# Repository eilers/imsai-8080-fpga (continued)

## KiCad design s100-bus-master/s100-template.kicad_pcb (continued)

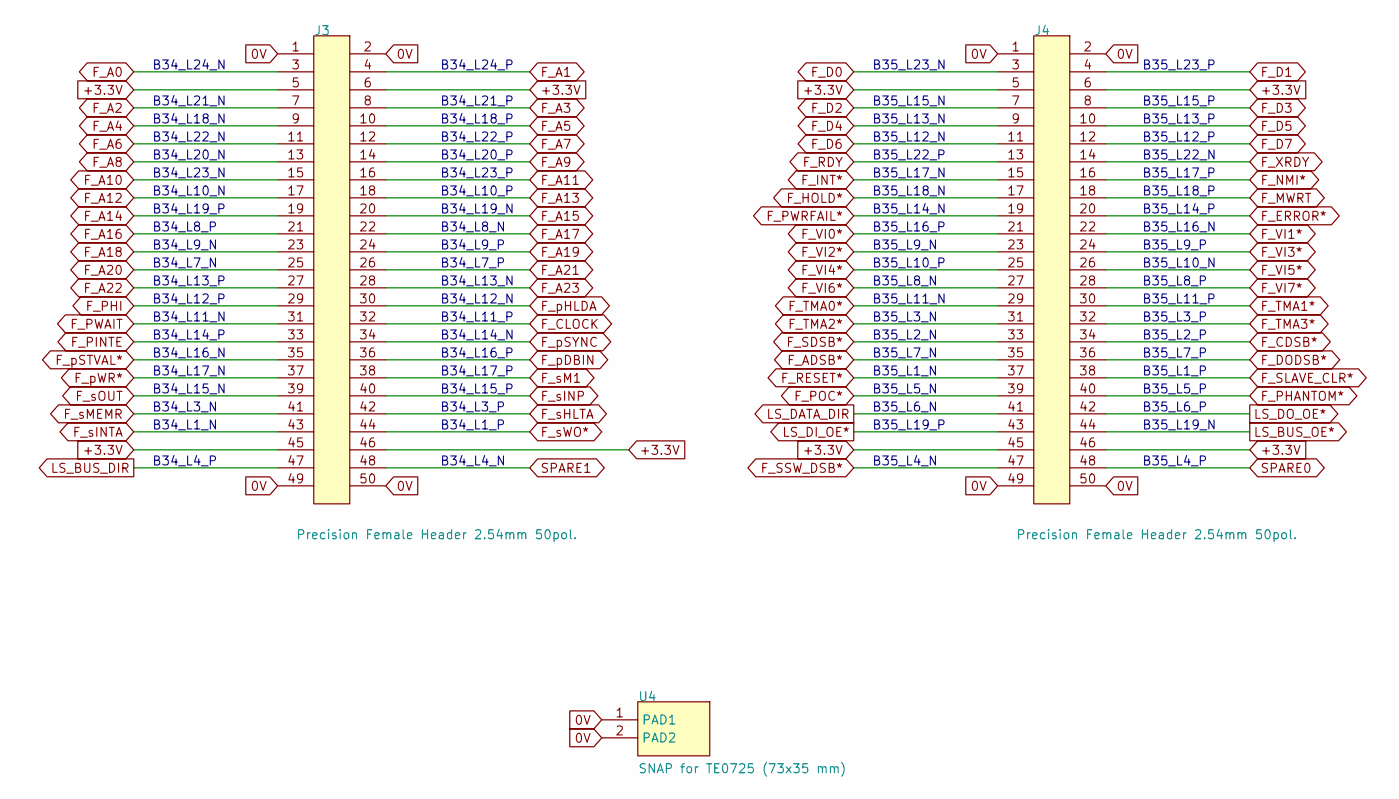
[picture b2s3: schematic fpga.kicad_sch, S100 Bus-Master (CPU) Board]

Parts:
J3, J4: Precision Female Header 2.54mm 50pol.; PinSocket_2x25_TE_North
U4: SNAP for TE0725 (73x35 mm); TE0725_Snap

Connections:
0V: J3.1, J3.2, J3.49, J3.50, J4.1, J4.2, J4.49, J4.50, U4.1, U4.2; also elsewhere on the board
+3.3V: J3.5, J3.6, J3.45, J3.46, J4.5, J4.6, J4.45, J4.46; also elsewhere on the board
F_A0: J3.3; also elsewhere on the board
F_A1: J3.4; also elsewhere on the board
F_A2: J3.7; also elsewhere on the board
F_A3: J3.8; also elsewhere on the board
F_A4: J3.9; also elsewhere on the board
F_A5: J3.10; also elsewhere on the board
F_A6: J3.11; also elsewhere on the board
F_A7: J3.12; also elsewhere on the board
F_A8: J3.13; also elsewhere on the board
F_A9: J3.14; also elsewhere on the board
F_A10: J3.15; also elsewhere on the board
F_A11: J3.16; also elsewhere on the board
F_A12: J3.17; also elsewhere on the board
F_A13: J3.18; also elsewhere on the board
F_A14: J3.19; also elsewhere on the board
F_A15: J3.20; also elsewhere on the board
F_A16: J3.21; also elsewhere on the board
F_A17: J3.22; also elsewhere on the board
F_A18: J3.23; also elsewhere on the board
F_A19: J3.24; also elsewhere on the board
F_A20: J3.25; also elsewhere on the board
F_A21: J3.26; also elsewhere on the board
F_A22: J3.27; also elsewhere on the board
F_A23: J3.28; also elsewhere on the board
F_ADSB*: J4.35; also elsewhere on the board
F_CDSB*: J4.34; also elsewhere on the board
F_CLOCK: J3.32; also elsewhere on the board
F_D0: J4.3; also elsewhere on the board
F_D1: J4.4; also elsewhere on the board
F_D2: J4.7; also elsewhere on the board
F_D3: J4.8; also elsewhere on the board
F_D4: J4.9; also elsewhere on the board
F_D5: J4.10; also elsewhere on the board
F_D6: J4.11; also elsewhere on the board
F_D7: J4.12; also elsewhere on the board
F_DODSB*: J4.36; also elsewhere on the board
F_ERROR*: J4.20; also elsewhere on the board
F_HOLD*: J4.17; also elsewhere on the board
F_INT*: J4.15; also elsewhere on the board
F_MWRT: J4.18; also elsewhere on the board
F_NMI*: J4.16; also elsewhere on the board
F_PHANTOM*: J4.40; also elsewhere on the board
F_PHI: J3.29; also elsewhere on the board
F_PINTE: J3.33; also elsewhere on the board
F_POC*: J4.39; also elsewhere on the board
F_PWAIT: J3.31; also elsewhere on the board
F_PWRFAIL*: J4.19; also elsewhere on the board
F_RDY: J4.13; also elsewhere on the board
F_RESET*: J4.37; also elsewhere on the board
F_SDSB*: J4.33; also elsewhere on the board
F_SLAVE_CLR*: J4.38; also elsewhere on the board
F_SSW_DSB*: J4.47; also elsewhere on the board
F_TMA0*: J4.29; also elsewhere on the board
F_TMA1*: J4.30; also elsewhere on the board
F_TMA2*: J4.31; also elsewhere on the board
F_TMA3*: J4.32; also elsewhere on the board
F_VI0*: J4.21; also elsewhere on the board
F_VI1*: J4.22; also elsewhere on the board
F_VI2*: J4.23; also elsewhere on the board
F_VI3*: J4.24; also elsewhere on the board
F_VI4*: J4.25; also elsewhere on the board
F_VI5*: J4.26; also elsewhere on the board
F_VI6*: J4.27; also elsewhere on the board
F_VI7*: J4.28; also elsewhere on the board
F_XRDY: J4.14; also elsewhere on the board
F_pDBIN: J3.36; also elsewhere on the board
F_pHLDA: J3.30; also elsewhere on the board
F_pSTVAL*: J3.35; also elsewhere on the board
F_pSYNC: J3.34; also elsewhere on the board
F_pWR*: J3.37; also elsewhere on the board
F_sHLTA: J3.42; also elsewhere on the board
F_sINP: J3.40; also elsewhere on the board
F_sINTA: J3.43; also elsewhere on the board
F_sM1: J3.38; also elsewhere on the board
F_sMEMR: J3.41; also elsewhere on the board
F_sOUT: J3.39; also elsewhere on the board
F_sWO*: J3.44; also elsewhere on the board
LS_BUS_DIR: J3.47; also elsewhere on the board
LS_BUS_OE*: J4.44; also elsewhere on the board
LS_DATA_DIR: J4.41; also elsewhere on the board
LS_DI_OE*: J4.43; also elsewhere on the board
LS_DO_OE*: J4.42; also elsewhere on the board
SPARE0: J4.48
SPARE1: J3.48

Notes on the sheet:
B34_L8_N
B35_L18_P
B34_L15_N
B35_L14_P
B35_L6_N
B35_L6_P
B35_L22_P
B35_L13_P
B35_L17_N
B34_L1_P
B35_L22_N
B34_L12_P
B35_L15_P
B34_L13_N
B34_L16_P
B34_L11_N
B34_L18_P
B35_L9_N
B35_L4_P
B35_L14_N
B35_L8_P
B35_L4_N
B34_L21_P
B34_L16_N
B34_L3_N
B35_L16_N
B35_L17_P
B34_L24_N
B34_L14_N
B35_L12_N
B35_L9_P
B34_L9_P
B35_L7_P
B35_L10_N
B35_L23_N
B34_L10_N
B34_L3_P
B34_L10_P
B34_L22_P
B35_L11_N

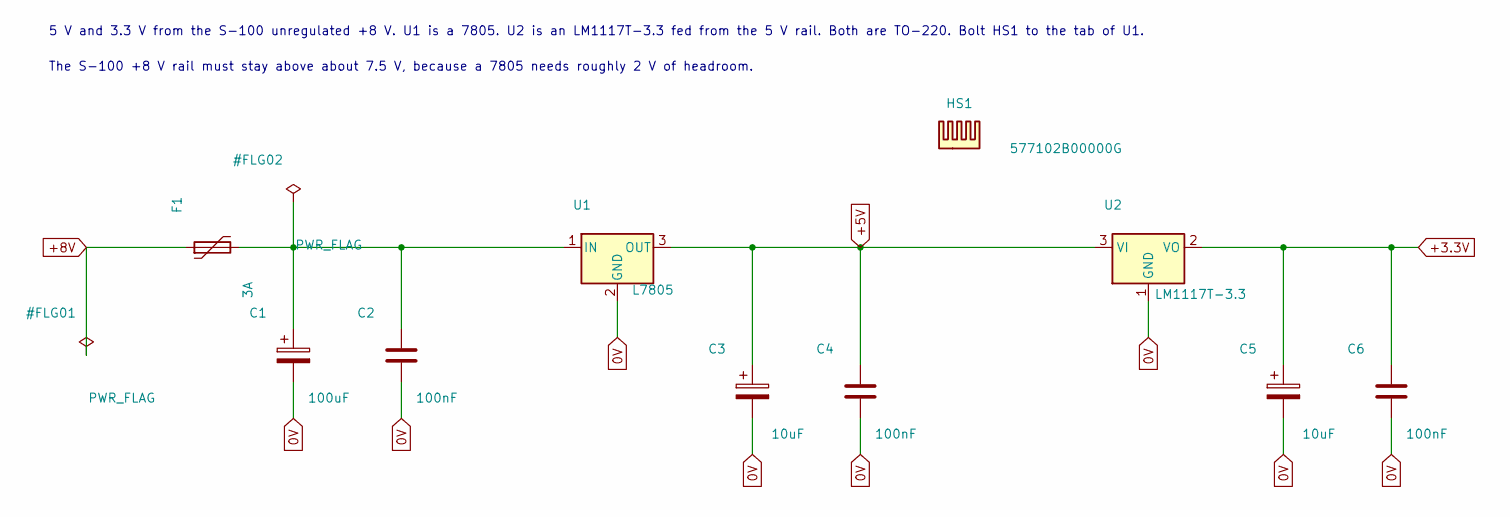
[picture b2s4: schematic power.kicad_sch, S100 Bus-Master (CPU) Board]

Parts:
C1: 100uF; CP_Radial_D10.0mm_P5.00mm
C2, C4, C6: 100nF; C_Disc_D5.0mm_W2.5mm_P5.00mm
C3, C5: 10uF; CP_Radial_D6.3mm_P2.50mm
F1: 3A; Fuse_Bourns_MF-RHT300
HS1: 577102B00000G
U1: L7805; TO-220-3_Vertical
U2: LM1117T-3.3; TO-220-3_Vertical

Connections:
0V: C1.2, C2.2, C3.2, C4.2, C5.2, C6.2, U1.2 (GND), U2.1 (GND); also elsewhere on the board
+3.3V: C5.1, C6.1, U2.2 (VO); also elsewhere on the board
+5V: C3.1, C4.1, U1.3 (OUT), U2.3 (VI); also elsewhere on the board
+8V: F1.1; also elsewhere on the board
unnamed: C1.1, C2.1, F1.2, U1.1 (IN)

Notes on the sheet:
The S-100 +8 V rail must stay above about 7.5 V, because a 7805 needs roughly 2 V of headroom.
5 V and 3.3 V from the S-100 unregulated +8 V. U1 is a 7805. U2 is an LM1117T-3.3 fed from the 5 V rail. Both are TO-220. Bolt HS1 to the tab of U1.

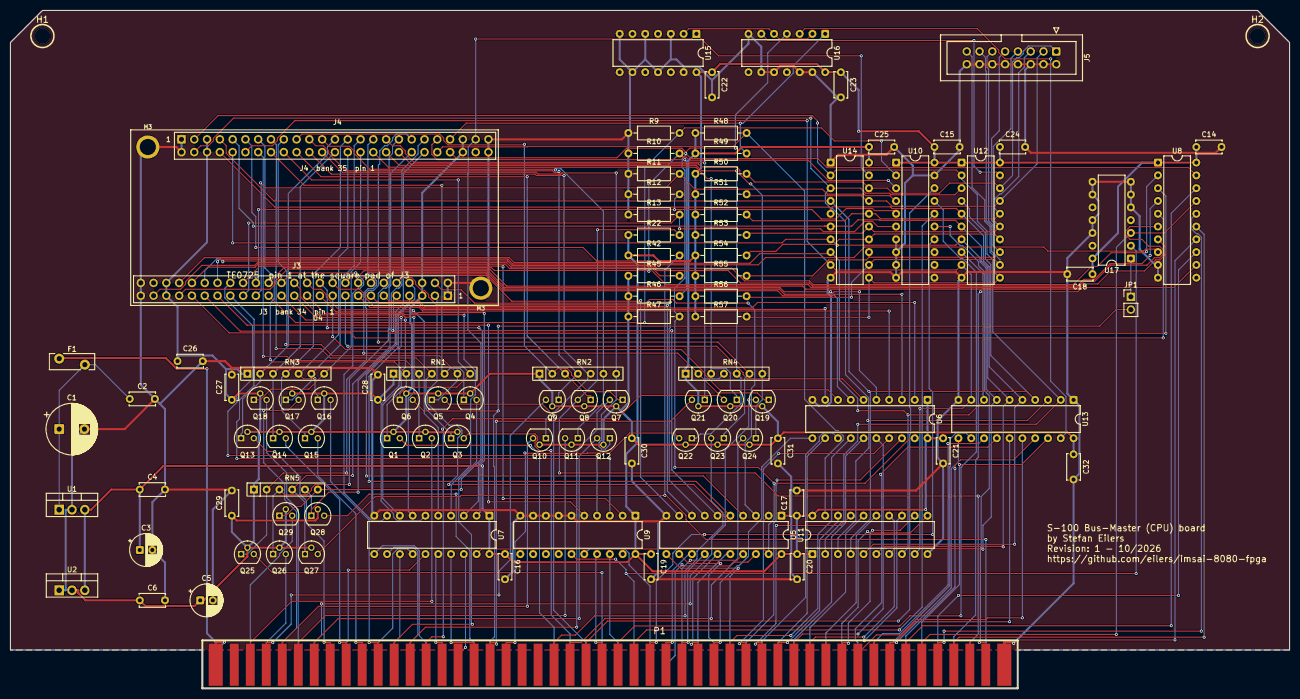
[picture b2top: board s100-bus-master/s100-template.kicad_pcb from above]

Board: 2 copper layers, 254.0 x 134.6 mm, 103 parts (0 on the bottom side), 184 nets.

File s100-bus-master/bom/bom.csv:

"Reference","Qty","Value","DNP","Exclude from BOM","Exclude from Board","Exclude from Simulation","Exclude from Position Files","Footprint","Datasheet"
"C1","1","100uF","","","","","${EXCLUDE_FROM_POS_FILES}","Capacitor_THT:CP_Radial_D10.0mm_P5.00mm",""
"C2,C4,C6,C14,C15,C16,C17,C18,C19,C20,C21,C22,C23,C24,C25,C26,C27,C28,C29,C30,C31,C32","22","100nF","","","","","${EXCLUDE_FROM_POS_FILES}","Capacitor_THT:C_Disc_D5.0mm_W2.5mm_P5.00mm",""
"C3,C5","2","10uF","","","","","${EXCLUDE_FROM_POS_FILES}","Capacitor_THT:CP_Radial_D6.3mm_P2.50mm",""
"F1","1","3A","","","","","${EXCLUDE_FROM_POS_FILES}","Fuse:Fuse_Bourns_MF-RHT300",""
"H1,H2","2","Ejector","","","","Excluded from simulation","${EXCLUDE_FROM_POS_FILES}","mals-library-pcb:s100-ejector",""
"HS1","1","577102B00000G","","","Excluded from board","Excluded from simulation","${EXCLUDE_FROM_POS_FILES}","","https://www.newark.com/boyd/577102b00000g/heat-sink/dp/18M8196"
"J3,J4","2","Precision Female Header 2.54mm 50pol.","","","","","${EXCLUDE_FROM_POS_FILES}","s100:PinSocket_2x25_TE_North",""
"J5","1","CP-A data cable","","","","","${EXCLUDE_FROM_POS_FILES}","Connector_IDC:IDC-Header_2x08_P2.54mm_Vertical",""
"JP1","1","open","","","","","${EXCLUDE_FROM_POS_FILES}","Connector_PinHeader_2.54mm:PinHeader_1x02_P2.54mm_Vertical",""
"P1","1","S100_MALE","","","","Excluded from simulation","${EXCLUDE_FROM_POS_FILES}","mals-library-pcb:s100-edge-connector-male",""
"Q1,Q2,Q3,Q4,Q5,Q6,Q7,Q8,Q9,Q10,Q11,Q12,Q13,Q14,Q15,Q16,Q17,Q18,Q19,Q20,Q21,Q22,Q23,Q24,Q25,Q26,Q27,Q28,Q29","29","TN0702N3-G","","","","","${EXCLUDE_FROM_POS_FILES}","Package_TO_SOT_THT:TO-92","https://www.microchip.com/en-us/product/tn0702"
"R9,R10,R11,R12,R13,R45,R46,R47,R48,R49","10","10k","","","","","${EXCLUDE_FROM_POS_FILES}","Resistor_THT:R_Axial_DIN0207_L6.3mm_D2.5mm_P10.16mm_Horizontal",""
"R22,R42","2","2.2k","","","","","${EXCLUDE_FROM_POS_FILES}","Resistor_THT:R_Axial_DIN0207_L6.3mm_D2.5mm_P10.16mm_Horizontal",""
"R50,R51,R52,R53,R54,R55,R56,R57","8","1k","","","","","${EXCLUDE_FROM_POS_FILES}","Resistor_THT:R_Axial_DIN0207_L6.3mm_D2.5mm_P10.16mm_Horizontal",""
"RN1,RN2,RN3,RN4","4","4607X-101-103","","","","","${EXCLUDE_FROM_POS_FILES}","Resistor_THT:R_Array_SIP7",""
"RN5","1","4606X-101-103","","","","","${EXCLUDE_FROM_POS_FILES}","Resistor_THT:R_Array_SIP6",""
"U1","1","L7805","","","","","${EXCLUDE_FROM_POS_FILES}","Package_TO_SOT_THT:TO-220-3_Vertical",""
"U2","1","LM1117T-3.3","","","","","${EXCLUDE_FROM_POS_FILES}","Package_TO_SOT_THT:TO-220-3_Vertical",""
"U4","1","SNAP for TE0725 (73x35 mm)","","","","","${EXCLUDE_FROM_POS_FILES}","s100:TE0725_Snap",""
"U5,U6,U7,U8,U9,U10,U11,U12","8","74ACT245","","","","","${EXCLUDE_FROM_POS_FILES}","Package_DIP:DIP-20_W7.62mm",""
"U13,U14","2","74LVC245","","","","","${EXCLUDE_FROM_POS_FILES}","Package_DIP:DIP-20_W7.62mm",""
"U15","1","74HCT04","","","","","${EXCLUDE_FROM_POS_FILES}","Package_DIP:DIP-14_W7.62mm",""
"U16","1","74HCT32","","","","","${EXCLUDE_FROM_POS_FILES}","Package_DIP:DIP-14_W7.62mm",""
"U17","1","74HCT02","","","","","${EXCLUDE_FROM_POS_FILES}","Package_DIP:DIP-14_W7.62mm",""

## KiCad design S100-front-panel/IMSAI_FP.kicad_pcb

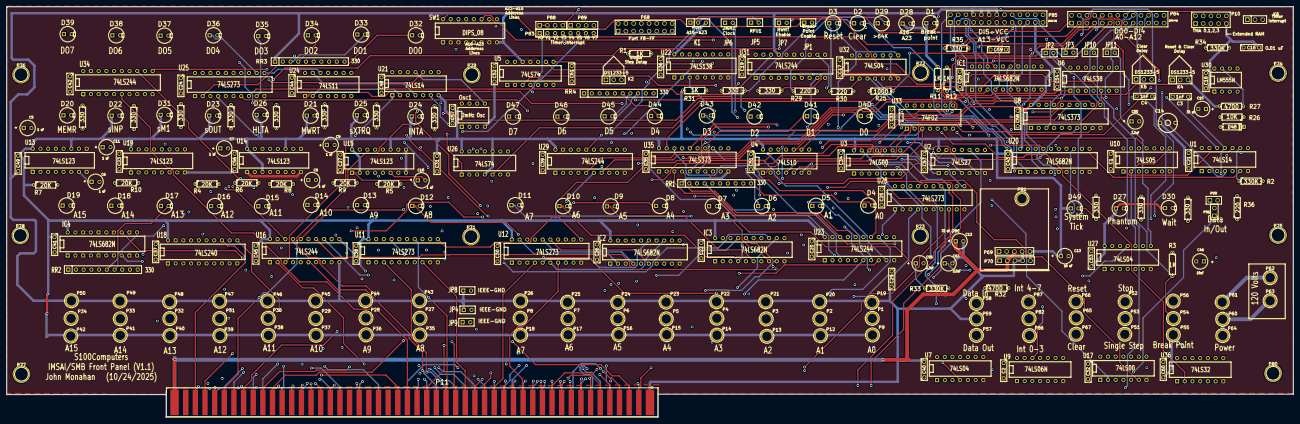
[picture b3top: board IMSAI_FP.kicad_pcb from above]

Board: 4 copper layers, 423.8 x 135.2 mm, 300 parts (0 on the bottom side), 335 nets.

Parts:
C1, C2, C17, C18, C19, C20, C21, C22, C23, C24, C25, C26, C27, C28, C29, C30, C31, C32, C33, C34, C35, C36, C37, C38, C39, C40, C41, C42, C43, C44, C45, C47, C48, C49, C51, C52, C53, C54, C56, C57, C58, C59, C60, C61: 0.1 uF; C2
C3, C4: 1nF; C2
C5, C6, C7, C8, C9, C10, C11: 1 uF; C1V5
C12: 33 uF (25V); C1V5
C13: 10 uF; C1V5
C14: CTRIM; CV3-30PF
C15: 33 uF; C1V5
C16: 0.01 uF; C2
C46: 10uF; C1V5
C50, C55, C62: 2.2uF; C1V5
D1, D2, D3, D4, D5, D6, D7, D8, D9, D10, D11, D12, D13, D14, D15, D16, D17, D18, D19, D20, D21, D22, D23, D24, D25, D26, D27, D28, D29, D30, D31, D32, D33, D34, D35, D36, D37, D38, D39, D40, D41, D42, D43, D44, D45, D46, D47, D49: LED; LEDV
D48: DIODE; D3
IC1, IC2, IC3, IC4: 74LS682N; DIP-20__300
JP1, JP2, JP3, JP4, JP5, JP6, JP7, JP8, JP9, JP10, JP11: JUMPER; SIL-2
K1: CONN_3; SIL-3
K2, K4, K5: DS1233-5; PIN_ARRAY_3X1
K6: CONN_3; PIN_ARRAY_3X1
Osc1: 2mHz Osc; DIP-8__300
P1, P2, P3, P4, P5, P6, P7, P8, P9, P12, P13, P14, P15, P16, P17, P18, P19, P20, P21, P22, P23, P24, P25, P26, P27, P28, P29, P30, P31, P32, P33, P34, P35, P36, P37, P38, P39, P40, P41, P42, P43, P44, P45, P46, P47, P48, P49, P50, P51, P52, P53, P54, P55, P56, P57, P58, P59, P60, P61, P62, P63, P64, P65, P66, P67, P71, P72, P73, P74, P75, P76, P77, P78, P79, P80, P81, P82, P86, P87: CONN_1; 1pin
P10: CONN_5X2; PIN_ARRAY_5x2
P11: S100_MALE
P68: CONN_8x2; pin_array_8x2
P69, P70: CONN_5; PIN_ARRAY_5x1
P83: CONN_8; SIL-8
P84, P85: CONN_13X2; pin_array_13x2
P88, P89: CONN_4; PIN_ARRAY_4x1
P90, P91: CONN_2; PIN_ARRAY_2X1
R1, R3, R11, R12, R31: 1K; R3
R2, R33, R34: 330K; R3
R4, R5, R6, R7, R8, R9, R10: 20K; R3
R13, R14, R15, R16, R17, R18, R19, R20, R21, R22, R23, R24, R28, R35: 330; R3
R25: 1000; R3
R26: 10K; R3
R27, R32: 4700; R3
R29, R30, R36: 220; R3
RR1, RR2: 330; SIL-10
RR3, RR4: 330; r_pack9
SW1: DIPS_08; DIP-16__300
U1, U21: 74LS14; DIP-14__300
U2: 74LS27; DIP-14__300
U3, U17: 74LS00; DIP-14__300
U4: 74LS10; DIP-14__300
U5, U26: 74LS74; DIP-14__300
U6: 74LS38; DIP-14__300
U7, U27, U32: 74LS04; DIP-14__300
U8, U35: 74LS373; DIP-20__300
U9: 74LS06N; DIP-14__300
U10: 74LS05; DIP-14__300
U11, U12, U25, U28: 74LS273; DIP-20__300
U13, U14, U15, U19: 74LS123; DIP-16__300
U16, U23, U29, U31, U34: 74LS244; DIP-20__300
U18: 74LS240; DIP-20__300
U20: 74LS682N; DIP-20__300
U22: 74LS138; DIP-16__300
U24: 74LS11; DIP-14__300
U30: LM555N; DIP-8__300
U33: 74F02; DIP-14__300
U36: 74LS32; DIP-14__300

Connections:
/2MHz_CLOCK: U18.2, U21.10
/+8V: C12.1, P11.1, P11.51, P69.3, P70.2
/>64K_LED: D29.2, R22.1
/A0: P11.79, U11.3
/A1: P11.80, U11.4
/A2: P11.81, U11.7
/A3: P11.31, U11.8
/A4: P11.30, U11.13
/A5: P11.29, U11.14
/A6: P11.82, U11.17
/A7: P11.83, U11.18
/A8: P11.84, U12.3
/A9: P11.34, U12.4
/A10: P11.37, U12.7
/A11: P11.87, U12.8
/A12: P11.33, U12.13
/A13: P11.85, U12.14
/A14: P11.86, U12.17
/A15: P11.32, U12.18
/A16: IC4.17, P11.16, U28.3, U31.3
/A17: IC4.15, P11.17, U28.4, U31.5
/A18: IC4.13, P11.15, U28.7, U31.7
/A19: IC4.11, P11.59, U28.8, U31.9
/A20: IC4.8, P11.61, U28.13, U31.12
/A21: IC4.6, P11.62, U28.14, U31.14
/A22: IC4.4, P11.63, U28.17, U31.16
/A23: IC4.2, P11.64, U28.18, U31.18
/ADD_LATCH: U3.11, U11.11, U12.11, U28.11
/BOARD_RESET*: D3.2, U11.1, U12.1, U28.1, U32.8
/B_A0: D4.1, IC3.17, P84.1, U11.2, U22.1
/B_A1: D5.1, IC3.15, P84.3, U11.5, U22.2
/B_A2: D6.1, IC3.13, P84.5, U11.6, U22.3
/B_A3: D7.1, IC3.11, P84.7, U4.11, U11.9
/B_A4: D8.1, IC3.8, P84.9, U4.10, U11.12
/B_A5: D9.1, IC3.6, P84.11, U4.9, U11.15
/B_A6: D10.1, IC3.4, P84.13, U4.5, U11.16
/B_A7: D11.1, IC3.2, P84.15, U4.4, U11.19
/B_A8: D12.1, IC2.17, P84.17, U12.2, U20.17
/B_A9: D13.1, IC2.15, P84.19, U12.5, U20.15
/B_A10: D14.1, IC2.13, P84.21, U12.6, U20.13
/B_A11: D15.1, IC2.11, P84.23, U12.9, U20.11
/B_A12: D16.1, IC2.8, P84.25, U12.12, U20.8
/B_A13: D17.1, IC2.6, P85.1, U12.15, U20.6
/B_A14: D18.1, IC2.4, P85.3, U12.16, U20.4
/B_A15: D19.1, IC2.2, P85.5, U12.19, U20.2
/B_A16: IC1.17, P85.7, U28.2
/B_A17: IC1.15, P85.9, U28.5
/B_A18: IC1.13, P85.11, U28.6
/B_A19: IC1.11, P85.13, U28.9
/B_A20: IC1.8, P85.15, U28.12
/B_A21: IC1.6, P85.17, U28.15
/B_A22: IC1.4, P85.19, U28.16
/B_A23: IC1.2, P85.21, U28.19
/B_DI0: P84.18, U8.3, U29.18
/B_DI1: P84.20, U8.4, U29.16
/B_DI2: P84.22, U8.7, U29.14
/B_DI3: P84.24, U8.8, U29.12
/B_DI4: P84.26, U8.13, U29.9
/B_DI5: P85.2, U8.14, U29.7
/B_DI6: P85.4, U8.17, U29.5
/B_DI7: P85.6, U8.18, U29.3
/B_DO0: P84.2, U23.18, U25.3, U35.3
/B_DO1: P84.4, U23.16, U25.4, U35.4
/B_DO2: P84.6, U23.14, U25.7, U35.7
/B_DO3: P84.8, U23.12, U25.8, U35.8
/B_DO4: P84.10, U23.9, U25.13, U35.13
/B_DO5: P84.12, U23.7, U25.14, U35.14
/B_DO6: P84.14, U23.5, U25.17, U35.17
/B_DO7: P84.16, U23.3, U25.18, U35.18
/B_EXTENDED_RAM_ENABLE*: R21.2, U34.9
/B_MWRT: U13.10, U34.7, U36.1
/B_PHANTOM*: R20.2, U16.5
/B_PHI*: JP5.1, U18.14
/B_RDY*: U2.10, U2.11, U18.5
/B_RESET*: U5.1, U24.3, U25.1, U26.1, U34.12
/B_SIXTN*: U16.12, U27.9
/B_XRDY*: U2.9, U18.7
/B_pDBIN: U16.14, U27.11
/B_pSTVAL*: U27.1, U34.14
/B_pSYNC: U1.3, U3.12, U4.1, U16.16
/B_pWR*: U7.3, U16.3, U21.1, U33.3
/B_sHLTA*: R19.2, U18.9
/B_sINP: U14.2, U16.7
/B_sINTA*: U15.1, U18.3, U30.4
/B_sM1: U19.2, U34.18
/B_sMEMR: U2.3, U13.2, U16.18
/B_sOUT: U14.10, U16.9, U24.1, U33.2, U36.2
/B_sXTRQ*: U32.1, U34.16
/CLOCK*: JP6.2, P11.49
/DATA0: D40.1, U8.2, U35.2
/DATA1: D41.1, U8.5, U35.5
/DATA2: D42.1, U8.6, U35.6
/DATA3: D43.1, U8.9, U35.9
/DATA4: D44.1, U8.12, U35.12
/DATA5: D45.1, U8.15, U35.15
/DATA6: D46.1, U8.16, U35.16
/DATA7: D47.1, U8.19, U35.19
/DI0: P11.95, U29.2
/DI1: P11.94, U29.4
/DI2: P11.41, U29.6
/DI3: P11.42, U29.8
/DI4: P11.91, U29.11
/DI5: P11.92, U29.13
/DI6: P11.93, U29.15
/DI7: P11.43, U29.17
/DO0: P11.36, U23.2
/DO1: P11.35, U23.4
/DO2: P11.88, U23.6
/DO3: P11.89, U23.8
/DO4: P11.38, U23.11
/DO5: P11.39, U23.13
/DO6: P11.40, U23.15
/DO7: P11.90, U23.17
/EXTENDED_RAM_ENABLE*: P10.2, P10.4, P10.6, P10.8, P10.10, R25.2, U17.4, U17.5, U34.11
/EXTENDED_RAM_ENABLE_LED: D28.2, R21.1
/HLTA_LED: D26.2, R19.1
/INTA_LED: D24.2, R17.1
/IN_LED: D22.2, R15.1
/LATCH_DATA_8: JP2.2, U8.11, U18.16
/LATCH_DATA_8*: JP10.2, U18.4, U27.10
/LATCH_DATA_16: JP11.2, U27.8, U27.13
/LATCH_DATA_16*: JP3.2, U27.12
/LOCAL_MWRT: JP7.1, U2.4, U2.5, U18.12
/LOCAL_MWRT*: U18.8, U33.1
/M1_LED: D31.2, R23.1
/MR_LED: D20.2, R13.1
/MWRT: JP7.2, P11.68, U34.13
/MW_LED: D21.2, R14.1
/OUT_LED: D23.2, R16.1
/PHANTOM*: P11.67, U16.15
/PHA_LED: D27.2, R20.1
/PHI: P11.24, U1.1, U18.6
/POC*: P11.99, U10.10
/PUA2: C6.1, R10.2, U13.7
/PUA3: C7.1, R6.2, U14.15
/RDY: P11.72, U18.15
/REQ_LED: D25.2, R18.1
/RESET*: P11.75, U10.4, U34.8
/RFU1: JP5.2, P11.27
/SIXTN*: P11.60, U16.8
/SLAVE_CLR*: D2.2, P11.54, U10.2, U10.8
/TMA0*: P10.1, P11.55
/TMA1*: P10.3, P11.56
/TMA2*: P10.5, P11.57
/TMA3*: P10.7, P11.14
/VI0*: P11.4, P83.1
/VI1*: P11.5, P83.2
/VI2*: P11.6, P83.3
/VI3*: P11.7, P83.4
/VI4*: P11.8, P83.5
/VI5*: P11.9, P83.6
/VI6*: P11.10, P83.7
/VI7*: P11.11, P83.8
/WAIT_LED: D30.2, R24.1
/XRDY: JP1.1, P11.3, U6.3, U18.13
/pDBIN: P11.78, U16.6
/pSTVAL*: P11.25, U34.6
/pSYNC: P11.76, U16.4
/pWR*: P11.77, U16.17
/sHLTA: P11.48, U18.11
/sINP: P11.46, U16.13
/sINTA: P11.96, U18.17
/sM1: P11.44, U34.2
/sMEMR: P11.47, U16.2
/sOUT: P11.45, U16.11
/sXTRQ*: P11.58, U34.4
GND: C1.2, C2.2, C3.2, C4.2, C12.2, C13.2, C14.2, C15.2, C16.2, C17.2, C18.2, C19.2, C20.2, C21.2, C22.2, C23.2, C24.2, C25.2, C26.2, C27.2, C28.2, C29.2, C30.2, C31.2, C32.2, C33.2, C34.2, C35.2, C36.2, C37.2, C38.2, C39.2, C40.2, C41.2, C42.2, C43.2, C44.2, C45.2, C46.2, C47.2, C48.2, C49.2, C50.2, C51.2, C52.2, C53.2, C54.2, C55.2, C56.2, C57.2, C58.2, C59.2, C60.2, C61.2, C62.2, IC1.10, IC2.10, IC3.10, IC4.3, IC4.5, IC4.7, IC4.9, IC4.10, IC4.12, IC4.14, IC4.16, IC4.18, JP4.1, JP8.1, JP9.1, K2.1, K4.1, K5.1, Osc1.4, P10.9, P11.50, P11.100, P19.1, P20.1, P21.1, P22.1, P23.1, P24.1, P25.1, P26.1, P43.1, P44.1, P45.1, P46.1, P47.1, P48.1, P49.1, P50.1, P53.1, P55.1, P59.1, P65.1, P69.4, P70.3, P70.4, P85.8, P85.10, P85.12, P85.14, R3.1, RR1.1, RR2.1, RR3.1, RR4.1, SW1.1, SW1.2, SW1.3, SW1.4, SW1.5, SW1.6, SW1.7, SW1.8, U1.7, U2.7, U3.7, U4.7, U5.2, U5.7, U5.11, U5.12, U6.7, U7.7, U8.10, U9.7, U10.7, U11.10, U12.10, U13.1, U13.8, U13.9, U14.1, U14.8, U14.9, U15.8, U15.9, U16.1, U16.10, U16.19, U17.7, U18.1, U18.10, U18.19, U19.1, U19.8, U20.3, U20.5, U20.7, U20.9, U20.10, U20.12, U20.14, U20.16, U20.18, U21.7, U22.8, U23.1, U23.10, U23.19, U24.7, U25.10, U26.7, U27.7, U28.10, U29.1, U29.10, U29.19, U30.1, U31.2, U31.4, U31.6, U31.8, U31.10, U31.11, U31.13, U31.15, U31.17, U32.7, U33.7, U34.1, U34.10, U34.19, U35.10, U36.7
unnamed: D36.2, RR3.6
unnamed: D39.2, RR3.9
unnamed: D38.2, RR3.8
unnamed: D37.2, RR3.7
unnamed: D35.2, RR3.5
unnamed: D34.2, RR3.4
unnamed: D33.2, RR3.3
unnamed: D32.2, RR3.2
unnamed: D40.2, RR4.2
unnamed: D38.1, U25.16
unnamed: D39.1, U25.19
unnamed: D37.1, U25.15
unnamed: D36.1, U25.12
unnamed: D34.1, U25.6
unnamed: D33.1, U25.5
unnamed: D32.1, U25.2
unnamed: D35.1, U25.9
unnamed: U17.6, U31.1, U31.19
unnamed: D44.2, RR4.6
unnamed: D43.2, RR4.5
unnamed: D42.2, RR4.4
unnamed: D41.2, RR4.3
unnamed: U24.12, U25.11
unnamed: D47.2, RR4.9
unnamed: D46.2, RR4.8
unnamed: D45.2, RR4.7
unnamed: IC4.19, U17.1
unnamed: JP6.1, U18.18
unnamed: C10.1, R5.2, U15.7
unnamed: C9.1, R9.2, U15.15
unnamed: C8.1, R8.2, U14.7
unnamed: D16.2, RR2.6
unnamed: D19.2, RR2.9
unnamed: D18.2, RR2.8
unnamed: D17.2, RR2.7
unnamed: D15.2, RR2.5
unnamed: D14.2, RR2.4
unnamed: D13.2, RR2.3
unnamed: D12.2, RR2.2
unnamed: C5.1, R7.2, U13.15
unnamed: U21.2, U24.2
unnamed: R31.1, U22.6
unnamed: P68.2, P68.4, P68.6, P68.8, P68.10, P68.12, P68.14, P68.16, U21.3
unnamed: U21.4, U24.13
unnamed: K1.2, U4.3
unnamed: K1.1, U1.12
unnamed: U17.2, U32.4
unnamed: U4.8, U22.4
unnamed: U4.6, U22.5
unnamed: U5.9, U6.4
unnamed: JP1.2, U6.6
unnamed: Osc1.5, U21.11
unnamed: U21.6, U26.11
unnamed: C55.1, P57.1, R33.1, U21.5
unnamed: D3.1, R30.2
unnamed: C4.1, K5.2, P66.1, R12.1, U32.5
unnamed: C11.1, R4.2, U19.15
unnamed: U26.2, U26.6
unnamed: U6.1, U26.5
unnamed: U1.8, U26.3
unnamed: C50.1, P52.1, R2.1, U1.9
unnamed: C3.1, K4.2, P67.1, R11.1, U1.11
unnamed: U1.10, U10.1
unnamed: D2.1, R29.2
unnamed: D48.2, R26.1, R27.2, U30.7
unnamed: C16.1, U30.5
unnamed: C14.1, C15.1, D48.1, R26.2, U30.2, U30.6
unnamed: R28.2, U21.9, U30.3
unnamed: U3.13, U27.2
unnamed: U15.10, U32.2
unnamed: U1.5, U7.2
unnamed: U24.6, U26.13
unnamed: C46.1, K2.2, P51.1, R1.1, U7.1
unnamed: U24.8, U35.11
unnamed: U4.12, U5.10
unnamed: P54.1, R3.2, U5.13, U6.5
unnamed: C62.1, P58.1, R34.1, U24.4, U24.5
unnamed: K6.2, P82.1, R32.2, U9.12
unnamed: U7.4, U24.10, U24.11
unnamed: U24.9, U36.3
unnamed: U7.9, U26.8, U26.12, U35.1
unnamed: U7.5, U8.1, U26.9
unnamed: P90.1, U7.8
unnamed: P91.1, U7.6
unnamed: P90.2, P91.2, R36.2
unnamed: JP2.1, P85.16
unnamed: JP3.1, P85.18
unnamed: U10.3, U10.9, U10.11, U32.6, U32.9
unnamed: U1.6, U5.3
unnamed: U1.4, U5.4
unnamed: U5.5, U6.2, U10.6
unnamed: R35.1, U5.8, U10.5
unnamed: D1.2, R35.2
unnamed: JP4.2, P11.20
unnamed: JP10.1, P85.20
unnamed: JP11.1, P85.22
unnamed: IC3.16, P2.1
unnamed: IC3.18, P1.1
unnamed: IC3.14, P3.1
unnamed: IC3.12, P4.1
unnamed: IC3.9, P5.1
unnamed: IC3.7, P6.1
unnamed: IC3.5, P7.1
unnamed: IC3.3, P8.1
unnamed: IC3.19, U2.13
unnamed: IC1.19, U2.1
unnamed: U2.12, U4.13
unnamed: IC2.19, U2.2
unnamed: U1.2, U4.2
unnamed: D8.2, RR1.6
unnamed: D7.2, RR1.5
unnamed: D6.2, RR1.4
unnamed: D5.2, RR1.3
unnamed: D4.2, RR1.2
unnamed: D11.2, RR1.9
unnamed: D10.2, RR1.8
unnamed: D9.2, RR1.7
unnamed: P60.1, P63.1, P64.1
unnamed: P61.1, P62.1
unnamed: JP9.2, P11.53
unnamed: JP8.2, P11.70
unnamed: C10.2, U15.6
unnamed: R15.2, U14.4
unnamed: C7.2, U14.14
unnamed: R16.2, U14.12
unnamed: C8.2, U14.6
unnamed: R17.2, U15.4
unnamed: R18.2, U15.12
unnamed: C9.2, U15.14
unnamed: R24.2, U2.8
unnamed: R22.2, U17.3
unnamed: U2.6, U32.3
unnamed: R13.2, U13.4
unnamed: C5.2, U13.14
unnamed: C6.2, U13.6
unnamed: R14.2, U13.12
unnamed: IC1.18, SW1.9
unnamed: IC1.16, SW1.10
unnamed: IC1.14, SW1.11
unnamed: IC1.12, SW1.12
unnamed: IC1.9, SW1.13
unnamed: IC1.7, SW1.14
unnamed: IC1.5, SW1.15
unnamed: IC1.3, SW1.16
unnamed: IC2.3, P34.1
unnamed: IC2.5, P33.1
unnamed: IC2.7, P32.1
unnamed: IC2.9, P31.1
unnamed: IC2.12, P30.1
unnamed: IC2.14, P29.1
unnamed: IC2.16, P28.1
unnamed: IC2.18, P27.1
unnamed: K6.1, P86.1, P88.1, P88.2, P88.3, P88.4
unnamed: K6.3, P87.1, P89.1, P89.2, P89.3, P89.4
unnamed: U9.13, U21.8
unnamed: P68.3, U22.14
unnamed: P68.1, U22.15
unnamed: P68.5, U22.13
unnamed: P68.7, U22.12
unnamed: P68.9, U22.11
unnamed: P68.11, U22.10
unnamed: P68.13, U22.9
unnamed: P68.15, U22.7
unnamed: U1.13, U20.19
unnamed: R23.2, U19.4
unnamed: C11.2, U19.14
unnamed: D49.2, R28.1
VCC: C1.1, C2.1, C13.1, C17.1, C18.1, C19.1, C20.1, C21.1, C22.1, C23.1, C24.1, C25.1, C26.1, C27.1, C28.1, C29.1, C30.1, C31.1, C32.1, C33.1, C34.1, C35.1, C36.1, C37.1, C38.1, C39.1, C40.1, C41.1, C42.1, C43.1, C44.1, C45.1, C47.1, C48.1, C49.1, C51.1, C52.1, C53.1, C54.1, C56.1, C57.1, C58.1, C59.1, C60.1, C61.1, D1.1, D20.1, D21.1, D22.1, D23.1, D24.1, D25.1, D26.1, D27.1, D28.1, D29.1, D30.1, D31.1, D49.1, IC1.20, IC2.20, IC3.20, IC4.20, K1.3, K2.3, K4.3, K5.3, Osc1.8, P9.1, P12.1, P13.1, P14.1, P15.1, P16.1, P17.1, P18.1, P35.1, P36.1, P37.1, P38.1, P39.1, P40.1, P41.1, P42.1, P56.1, P69.5, P70.5, P85.23, P85.24, P85.25, R1.2, R2.2, R4.1, R5.1, R6.1, R7.1, R8.1, R9.1, R10.1, R11.2, R12.2, R25.1, R27.1, R29.1, R30.1, R31.2, R32.1, R33.2, R34.2, R36.1, U1.14, U2.14, U3.14, U4.14, U5.14, U6.14, U7.14, U8.20, U9.14, U10.14, U11.20, U12.20, U13.3, U13.11, U13.16, U14.3, U14.11, U14.16, U15.2, U15.3, U15.11, U15.16, U16.20, U17.14, U18.20, U19.3, U19.16, U20.20, U21.14, U22.16, U23.20, U24.14, U25.20, U26.4, U26.10, U26.14, U27.14, U28.20, U29.20, U30.8, U31.20, U32.14, U33.14, U34.20, U35.20, U36.14

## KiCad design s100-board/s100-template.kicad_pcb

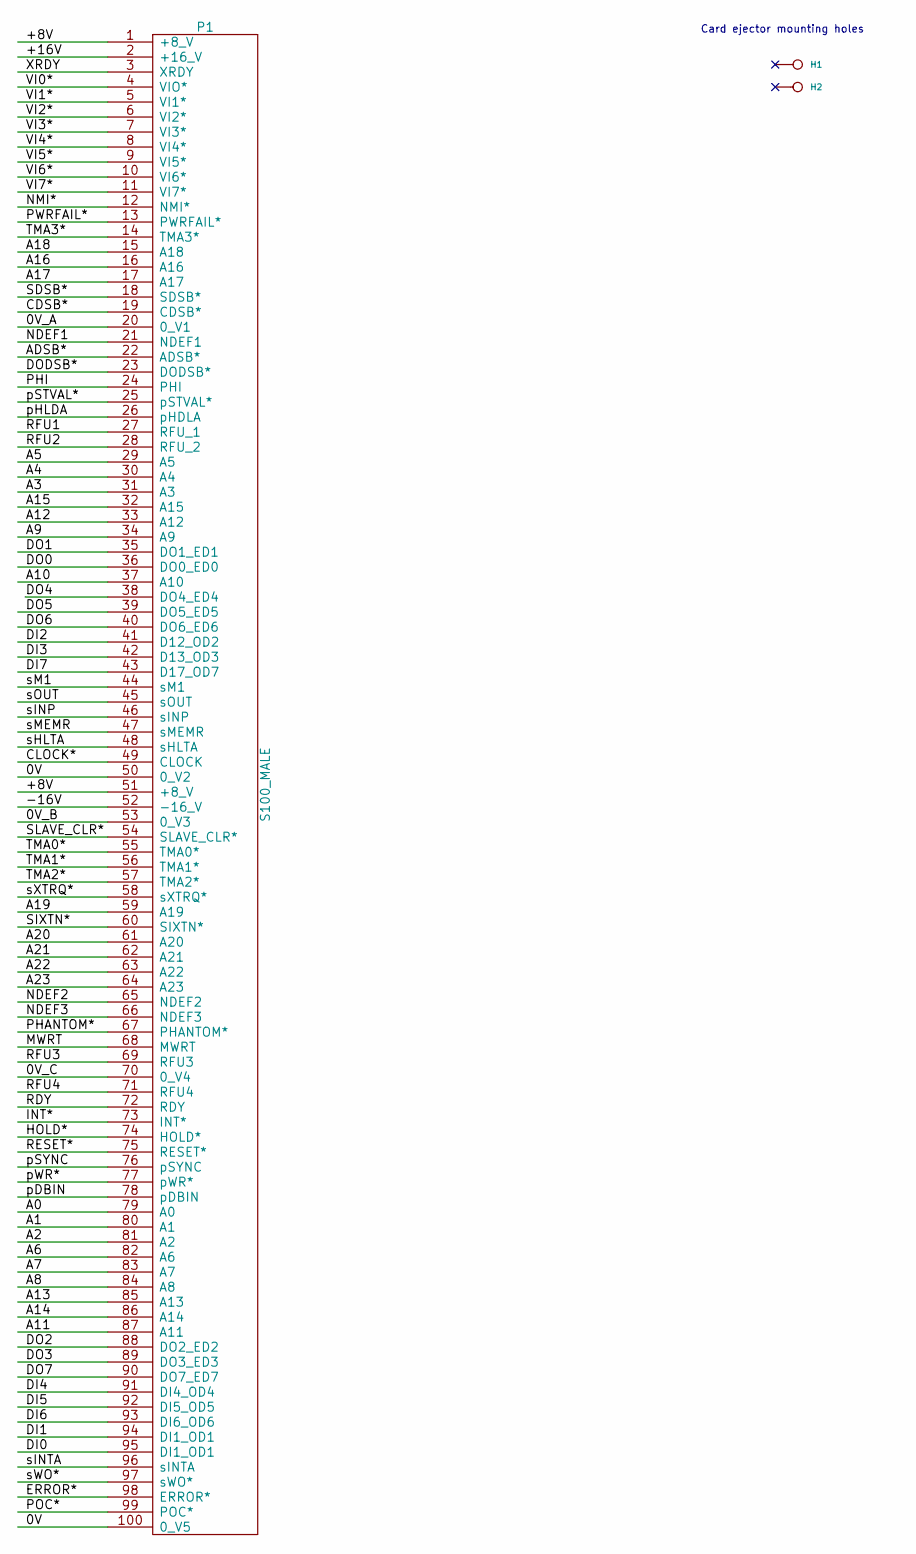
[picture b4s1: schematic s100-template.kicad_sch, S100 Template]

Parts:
H1, H2: Ejector; s100-ejector
P1: S100_MALE; s100-edge-connector-male

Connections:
/0V: P1.50 (0_V2), P1.100 (0_V5)
/0V_A: P1.20 (0_V1)
/0V_B: P1.53 (0_V3)
/0V_C: P1.70 (0_V4)
/+8V: P1.1 (+8_V), P1.51 (+8_V)
/+16V: P1.2 (+16_V)
/-16V: P1.52 (-16_V)
/A0: P1.79 (A0)
/A1: P1.80 (A1)
/A2: P1.81 (A2)
/A3: P1.31 (A3)
/A4: P1.30 (A4)
/A5: P1.29 (A5)
/A6: P1.82 (A6)
/A7: P1.83 (A7)
/A8: P1.84 (A8)
/A9: P1.34 (A9)
/A10: P1.37 (A10)
/A11: P1.87 (A11)
/A12: P1.33 (A12)
/A13: P1.85 (A13)
/A14: P1.86 (A14)
/A15: P1.32 (A15)
/A16: P1.16 (A16)
/A17: P1.17 (A17)
/A18: P1.15 (A18)
/A19: P1.59 (A19)
/A20: P1.61 (A20)
/A21: P1.62 (A21)
/A22: P1.63 (A22)
/A23: P1.64 (A23)
/ADSB*: P1.22 (ADSB*)
/CDSB*: P1.19 (CDSB*)
/CLOCK*: P1.49 (CLOCK)
/DI0: P1.95 (DI1_OD1)
/DI1: P1.94 (DI1_OD1)
/DI2: P1.41 (D12_OD2)
/DI3: P1.42 (D13_OD3)
/DI4: P1.91 (DI4_OD4)
/DI5: P1.92 (DI5_OD5)
/DI6: P1.93 (DI6_OD6)
/DI7: P1.43 (D17_OD7)
/DO0: P1.36 (DO0_ED0)
/DO1: P1.35 (DO1_ED1)
/DO2: P1.88 (DO2_ED2)
/DO3: P1.89 (DO3_ED3)
/DO4: P1.38 (DO4_ED4)
/DO5: P1.39 (DO5_ED5)
/DO6: P1.40 (DO6_ED6)
/DO7: P1.90 (DO7_ED7)
/DODSB*: P1.23 (DODSB*)
/ERROR*: P1.98 (ERROR*)
/HOLD*: P1.74 (HOLD*)
/INT*: P1.73 (INT*)
/MWRT: P1.68 (MWRT)
/NDEF1: P1.21 (NDEF1)
/NDEF2: P1.65 (NDEF2)
/NDEF3: P1.66 (NDEF3)
/NMI*: P1.12 (NMI*)
/PHANTOM*: P1.67 (PHANTOM*)
/PHI: P1.24 (PHI)
/POC*: P1.99 (POC*)
/PWRFAIL*: P1.13 (PWRFAIL*)
/RDY: P1.72 (RDY)
/RESET*: P1.75 (RESET*)
/RFU1: P1.27 (RFU_1)
/RFU2: P1.28 (RFU_2)
/RFU3: P1.69 (RFU3)
/RFU4: P1.71 (RFU4)
/SDSB*: P1.18 (SDSB*)
/SIXTN*: P1.60 (SIXTN*)
/SLAVE_CLR*: P1.54 (SLAVE_CLR*)
/TMA0*: P1.55 (TMA0*)
/TMA1*: P1.56 (TMA1*)
/TMA2*: P1.57 (TMA2*)
/TMA3*: P1.14 (TMA3*)
/VI0*: P1.4 (VIO*)
/VI1*: P1.5 (VI1*)
/VI2*: P1.6 (VI2*)
/VI3*: P1.7 (VI3*)
/VI4*: P1.8 (VI4*)
/VI5*: P1.9 (VI5*)
/VI6*: P1.10 (VI6*)
/VI7*: P1.11 (VI7*)
/XRDY: P1.3 (XRDY)
/pDBIN: P1.78 (pDBIN)
/pHLDA: P1.26 (pHDLA)
/pSTVAL*: P1.25 (pSTVAL*)
/pSYNC: P1.76 (pSYNC)
/pWR*: P1.77 (pWR*)
/sHLTA: P1.48 (sHLTA)
/sINP: P1.46 (sINP)
/sINTA: P1.96 (sINTA)
/sM1: P1.44 (sM1)
/sMEMR: P1.47 (sMEMR)
/sOUT: P1.45 (sOUT)
/sWO*: P1.97 (sWO*)
/sXTRQ*: P1.58 (sXTRQ*)

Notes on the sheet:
Card ejector mounting holes

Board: 2 copper layers, 3 parts (0 on the bottom side), 2 nets, no tracks yet.

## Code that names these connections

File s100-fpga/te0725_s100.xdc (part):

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set_false_path -from [all_registers] -to [get_ports {f_* ls_* }]

## header J3 (bank 34)
set_property -dict {PACKAGE_PIN T8 IOSTANDARD LVCMOS33} [get_ports {f_a[0]}]  ;# F_A0 = J3-3 B34_L24_N
set_property -dict {PACKAGE_PIN R8 IOSTANDARD LVCMOS33} [get_ports {f_a[1]}]  ;# F_A1 = J3-4 B34_L24_P
set_property -dict {PACKAGE_PIN V9 IOSTANDARD LVCMOS33} [get_ports {f_a[2]}]  ;# F_A2 = J3-7 B34_L21_N
set_property -dict {PACKAGE_PIN U9 IOSTANDARD LVCMOS33} [get_ports {f_a[3]}]  ;# F_A3 = J3-8 B34_L21_P
set_property -dict {PACKAGE_PIN N6 IOSTANDARD LVCMOS33} [get_ports {f_a[4]}]  ;# F_A4 = J3-9 B34_L18_N
set_property -dict {PACKAGE_PIN M6 IOSTANDARD LVCMOS33} [get_ports {f_a[5]}]  ;# F_A5 = J3-10 B34_L18_P
set_property -dict {PACKAGE_PIN U6 IOSTANDARD LVCMOS33} [get_ports {f_a[6]}]  ;# F_A6 = J3-11 B34_L22_N
set_property -dict {PACKAGE_PIN U7 IOSTANDARD LVCMOS33} [get_ports {f_a[7]}]  ;# F_A7 = J3-12 B34_L22_P
set_property -dict {PACKAGE_PIN V6 IOSTANDARD LVCMOS33} [get_ports {f_a[8]}]  ;# F_A8 = J3-13 B34_L20_N
set_property -dict {PACKAGE_PIN V7 IOSTANDARD LVCMOS33} [get_ports {f_a[9]}]  ;# F_A9 = J3-14 B34_L20_P
set_property -dict {PACKAGE_PIN T6 IOSTANDARD LVCMOS33} [get_ports {f_a[10]}]  ;# F_A10 = J3-15 B34_L23_N
set_property -dict {PACKAGE_PIN R7 IOSTANDARD LVCMOS33} [get_ports {f_a[11]}]  ;# F_A11 = J3-16 B34_L23_P
set_property -dict {PACKAGE_PIN V4 IOSTANDARD LVCMOS33} [get_ports {f_a[12]}]  ;# F_A12 = J3-17 B34_L10_N
set_property -dict {PACKAGE_PIN V5 IOSTANDARD LVCMOS33} [get_ports {f_a[13]}]  ;# F_A13 = J3-18 B34_L10_P
set_property -dict {PACKAGE_PIN R6 IOSTANDARD LVCMOS33} [get_ports {f_a[14]}]  ;# F_A14 = J3-19 B34_L19_P
set_property -dict {PACKAGE_PIN R5 IOSTANDARD LVCMOS33} [get_ports {f_a[15]}]  ;# F_A15 = J3-20 B34_L19_N
set_property -dict {PACKAGE_PIN U4 IOSTANDARD LVCMOS33} [get_ports {f_a[16]}]  ;# F_A16 = J3-21 B34_L8_P
set_property -dict {PACKAGE_PIN U3 IOSTANDARD LVCMOS33} [get_ports {f_a[17]}]  ;# F_A17 = J3-22 B34_L8_N
set_property -dict {PACKAGE_PIN V2 IOSTANDARD LVCMOS33} [get_ports {f_a[18]}]  ;# F_A18 = J3-23 B34_L9_N
set_property -dict {PACKAGE_PIN U2 IOSTANDARD LVCMOS33} [get_ports {f_a[19]}]  ;# F_A19 = J3-24 B34_L9_P
set_property -dict {PACKAGE_PIN V1 IOSTANDARD LVCMOS33} [get_ports {f_a[20]}]  ;# F_A20 = J3-25 B34_L7_N
set_property -dict {PACKAGE_PIN U1 IOSTANDARD LVCMOS33} [get_ports {f_a[21]}]  ;# F_A21 = J3-26 B34_L7_P
set_property -dict {PACKAGE_PIN N5 IOSTANDARD LVCMOS33} [get_ports {f_a[22]}]  ;# F_A22 = J3-27 B34_L13_P MRCC
set_property -dict {PACKAGE_PIN P5 IOSTANDARD LVCMOS33} [get_ports {f_a[23]}]  ;# F_A23 = J3-28 B34_L13_N
set_property -dict {PACKAGE_PIN T5 IOSTANDARD LVCMOS33} [get_ports {f_phi}]  ;# F_PHI = J3-29 B34_L12_P MRCC
set_property -dict {PACKAGE_PIN T4 IOSTANDARD LVCMOS33} [get_ports {f_phlda}]  ;# F_pHLDA = J3-30 B34_L12_N
set_property -dict {PACKAGE_PIN T3 IOSTANDARD LVCMOS33} [get_ports {f_pwait}]  ;# F_PWAIT = J3-31 B34_L11_N
set_property -dict {PACKAGE_PIN R3 IOSTANDARD LVCMOS33} [get_ports {f_clock}]  ;# F_CLOCK = J3-32 B34_L11_P SRCC
set_property -dict {PACKAGE_PIN P4 IOSTANDARD LVCMOS33} [get_ports {f_pinte}]  ;# F_PINTE = J3-33 B34_L14_P SRCC
set_property -dict {PACKAGE_PIN P3 IOSTANDARD LVCMOS33} [get_ports {f_psync}]  ;# F_pSYNC = J3-34 B34_L14_N
set_property -dict {PACKAGE_PIN N4 IOSTANDARD LVCMOS33} [get_ports {f_pstval_n}]  ;# F_pSTVAL* = J3-35 B34_L16_N
set_property -dict {PACKAGE_PIN M4 IOSTANDARD LVCMOS33} [get_ports {f_pdbin}]  ;# F_pDBIN = J3-36 B34_L16_P
set_property -dict {PACKAGE_PIN T1 IOSTANDARD LVCMOS33} [get_ports {f_pwr_n}]  ;# F_pWR* = J3-37 B34_L17_N
set_property -dict {PACKAGE_PIN R1 IOSTANDARD LVCMOS33} [get_ports {f_sm1}]  ;# F_sM1 = J3-38 B34_L17_P
set_property -dict {PACKAGE_PIN R2 IOSTANDARD LVCMOS33} [get_ports {f_sout}]  ;# F_sOUT = J3-39 B34_L15_N
set_property -dict {PACKAGE_PIN P2 IOSTANDARD LVCMOS33} [get_ports {f_sinp}]  ;# F_sINP = J3-40 B34_L15_P
set_property -dict {PACKAGE_PIN N1 IOSTANDARD LVCMOS33} [get_ports {f_smemr}]  ;# F_sMEMR = J3-41 B34_L3_N
set_property -dict {PACKAGE_PIN N2 IOSTANDARD LVCMOS33} [get_ports {f_shlta}]  ;# F_sHLTA = J3-42 B34_L3_P
set_property -dict {PACKAGE_PIN M1 IOSTANDARD LVCMOS33} [get_ports {f_sinta}]  ;# F_sINTA = J3-43 B34_L1_N
set_property -dict {PACKAGE_PIN L1 IOSTANDARD LVCMOS33} [get_ports {f_swo_n}]  ;# F_sWO* = J3-44 B34_L1_P
set_property -dict {PACKAGE_PIN M3 IOSTANDARD LVCMOS33} [get_ports {ls_bus_dir}]  ;# LS_BUS_DIR = J3-47 B34_L4_P
set_property -dict {PACKAGE_PIN M2 IOSTANDARD LVCMOS33 PULLUP true} [get_ports {spare1}]  ;# SPARE1 = J3-48 B34_L4_N

## header J4 (bank 35)
set_property -dict {PACKAGE_PIN K1 IOSTANDARD LVCMOS33} [get_ports {f_d[0]}]  ;# F_D0 = J4-3 B35_L23_N
set_property -dict {PACKAGE_PIN K2 IOSTANDARD LVCMOS33} [get_ports {f_d[1]}]  ;# F_D1 = J4-4 B35_L23_P
set_property -dict {PACKAGE_PIN G2 IOSTANDARD LVCMOS33} [get_ports {f_d[2]}]  ;# F_D2 = J4-7 B35_L15_N
set_property -dict {PACKAGE_PIN H2 IOSTANDARD LVCMOS33} [get_ports {f_d[3]}]  ;# F_D3 = J4-8 B35_L15_P
set_property -dict {PACKAGE_PIN F3 IOSTANDARD LVCMOS33} [get_ports {f_d[4]}]  ;# F_D4 = J4-9 B35_L13_N
set_property -dict {PACKAGE_PIN F4 IOSTANDARD LVCMOS33} [get_ports {f_d[5]}]  ;# F_D5 = J4-10 B35_L13_P MRCC
set_property -dict {PACKAGE_PIN D3 IOSTANDARD LVCMOS33} [get_ports {f_d[6]}]  ;# F_D6 = J4-11 B35_L12_N
set_property -dict {PACKAGE_PIN E3 IOSTANDARD LVCMOS33} [get_ports {f_d[7]}]  ;# F_D7 = J4-12 B35_L12_P MRCC
set_property -dict {PACKAGE_PIN J3 IOSTANDARD LVCMOS33 PULLUP true} [get_ports {f_rdy}]  ;# F_RDY = J4-13 B35_L22_P
set_property -dict {PACKAGE_PIN J2 IOSTANDARD LVCMOS33 PULLUP true} [get_ports {f_xrdy}]  ;# F_XRDY = J4-14 B35_L22_N
set_property -dict {PACKAGE_PIN G1 IOSTANDARD LVCMOS33 PULLUP true} [get_ports {f_int_n}]  ;# F_INT* = J4-15 B35_L17_N
set_property -dict {PACKAGE_PIN H1 IOSTANDARD LVCMOS33 PULLUP true} [get_ports {f_nmi_n}]  ;# F_NMI* = J4-16 B35_L17_P
set_property -dict {PACKAGE_PIN E1 IOSTANDARD LVCMOS33 PULLUP true} [get_ports {f_hold_n}]  ;# F_HOLD* = J4-17 B35_L18_N
set_property -dict {PACKAGE_PIN F1 IOSTANDARD LVCMOS33 PULLUP true} [get_ports {f_mwrt}]  ;# F_MWRT = J4-18 B35_L18_P
set_property -dict {PACKAGE_PIN D2 IOSTANDARD LVCMOS33 PULLUP true} [get_ports {f_pwrfail_n}]  ;# F_PWRFAIL* = J4-19 B35_L14_N
set_property -dict {PACKAGE_PIN E2 IOSTANDARD LVCMOS33 PULLUP true} [get_ports {f_error_n}]  ;# F_ERROR* = J4-20 B35_L14_P SRCC
set_property -dict {PACKAGE_PIN C2 IOSTANDARD LVCMOS33 PULLUP true} [get_ports {f_vi_n[0]}]  ;# F_VI0* = J4-21 B35_L16_P
set_property -dict {PACKAGE_PIN C1 IOSTANDARD LVCMOS33 PULLUP true} [get_ports {f_vi_n[1]}]  ;# F_VI1* = J4-22 B35_L16_N
set_property -dict {PACKAGE_PIN A1 IOSTANDARD LVCMOS33 PULLUP true} [get_ports {f_vi_n[2]}]  ;# F_VI2* = J4-23 B35_L9_N
set_property -dict {PACKAGE_PIN B1 IOSTANDARD LVCMOS33 PULLUP true} [get_ports {f_vi_n[3]}]  ;# F_VI3* = J4-24 B35_L9_P
set_property -dict {PACKAGE_PIN B3 IOSTANDARD LVCMOS33 PULLUP true} [get_ports {f_vi_n[4]}]  ;# F_VI4* = J4-25 B35_L10_P
set_property -dict {PACKAGE_PIN B2 IOSTANDARD LVCMOS33 PULLUP true} [get_ports {f_vi_n[5]}]  ;# F_VI5* = J4-26 B35_L10_N
set_property -dict {PACKAGE_PIN A3 IOSTANDARD LVCMOS33 PULLUP true} [get_ports {f_vi_n[6]}]  ;# F_VI6* = J4-27 B35_L8_N
set_property -dict {PACKAGE_PIN A4 IOSTANDARD LVCMOS33 PULLUP true} [get_ports {f_vi_n[7]}]  ;# F_VI7* = J4-28 B35_L8_P
set_property -dict {PACKAGE_PIN D4 IOSTANDARD LVCMOS33 PULLUP true} [get_ports {f_tma_n[0]}]  ;# F_TMA0* = J4-29 B35_L11_N
set_property -dict {PACKAGE_PIN D5 IOSTANDARD LVCMOS33 PULLUP true} [get_ports {f_tma_n[1]}]  ;# F_TMA1* = J4-30 B35_L11_P SRCC
set_property -dict {PACKAGE_PIN A5 IOSTANDARD LVCMOS33 PULLUP true} [get_ports {f_tma_n[2]}]  ;# F_TMA2* = J4-31 B35_L3_N
set_property -dict {PACKAGE_PIN A6 IOSTANDARD LVCMOS33 PULLUP true} [get_ports {f_tma_n[3]}]  ;# F_TMA3* = J4-32 B35_L3_P
set_property -dict {PACKAGE_PIN B6 IOSTANDARD LVCMOS33 PULLUP true} [get_ports {f_sdsb_n}]  ;# F_SDSB* = J4-33 B35_L2_N
set_property -dict {PACKAGE_PIN B7 IOSTANDARD LVCMOS33 PULLUP true} [get_ports {f_cdsb_n}]  ;# F_CDSB* = J4-34 B35_L2_P
set_property -dict {PACKAGE_PIN B4 IOSTANDARD LVCMOS33 PULLUP true} [get_ports {f_adsb_n}]  ;# F_ADSB* = J4-35 B35_L7_N
set_property -dict {PACKAGE_PIN C4 IOSTANDARD LVCMOS33 PULLUP true} [get_ports {f_dodsb_n}]  ;# F_DODSB* = J4-36 B35_L7_P
set_property -dict {PACKAGE_PIN C5 IOSTANDARD LVCMOS33 PULLUP true} [get_ports {f_reset_n}]  ;# F_RESET* = J4-37 B35_L1_N
set_property -dict {PACKAGE_PIN C6 IOSTANDARD LVCMOS33 PULLUP true} [get_ports {f_slave_clr_n}]  ;# F_SLAVE_CLR* = J4-38 B35_L1_P
set_property -dict {PACKAGE_PIN E5 IOSTANDARD LVCMOS33 PULLUP true} [get_ports {f_poc_n}]  ;# F_POC* = J4-39 B35_L5_N
set_property -dict {PACKAGE_PIN E6 IOSTANDARD LVCMOS33 PULLUP true} [get_ports {f_phantom_n}]  ;# F_PHANTOM* = J4-40 B35_L5_P
set_property -dict {PACKAGE_PIN D7 IOSTANDARD LVCMOS33} [get_ports {ls_data_dir}]  ;# LS_DATA_DIR = J4-41 B35_L6_N
set_property -dict {PACKAGE_PIN E7 IOSTANDARD LVCMOS33} [get_ports {ls_do_oe_n}]  ;# LS_DO_OE* = J4-42 B35_L6_P
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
